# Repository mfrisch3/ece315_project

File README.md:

# starter-project

## Getting started

To make it easy for you to get started with GitLab, here's a list of recommended next steps.

Already a pro? Just edit this README.md and make it your own. Want to make it easy? [Use the template at the bottom](#editing-this-readme)!

## Add your files

- [ ] [Create](https://docs.gitlab.com/ee/user/project/repository/web_editor.html#create-a-file) or [upload](https://docs.gitlab.com/ee/user/project/repository/web_editor.html#upload-a-file) files
- [ ] [Add files using the command line](https://docs.gitlab.com/ee/gitlab-basics/add-file.html#add-a-file-using-the-command-line) or push an existing Git repository with the following command:

```
cd existing_repo
git remote add origin https://git.doit.wisc.edu/engr/ece/cmpe_courses/public/ece315/mtb/f23/starter-project.git
git branch -M main
git push -uf origin main
```

## Integrate with your tools

- [ ] [Set up project integrations](https://git.doit.wisc.edu/engr/ece/cmpe_courses/public/ece315/mtb/f23/starter-project/-/settings/integrations)

## Collaborate with your team

- [ ] [Invite team members and collaborators](https://docs.gitlab.com/ee/user/project/members/)
- [ ] [Create a new merge request](https://docs.gitlab.com/ee/user/project/merge_requests/creating_merge_requests.html)
- [ ] [Automatically close issues from merge requests](https://docs.gitlab.com/ee/user/project/issues/managing_issues.html#closing-issues-automatically)
- [ ] [Enable merge request approvals](https://docs.gitlab.com/ee/user/project/merge_requests/approvals/)
- [ ] [Set auto-merge](https://docs.gitlab.com/ee/user/project/merge_requests/merge_when_pipeline_succeeds.html)

## Test and Deploy

Use the built-in continuous integration in GitLab.

- [ ] [Get started with GitLab CI/CD](https://docs.gitlab.com/ee/ci/quick_start/index.html)
- [ ] [Analyze your code for known vulnerabilities with Static Application Security Testing(SAST)](https://docs.gitlab.com/ee/user/application_security/sast/)
- [ ] [Deploy to Kubernetes, Amazon EC2, or Amazon ECS using Auto Deploy](https://docs.gitlab.com/ee/topics/autodevops/requirements.html)
- [ ] [Use pull-based deployments for improved Kubernetes management](https://docs.gitlab.com/ee/user/clusters/agent/)
- [ ] [Set up protected environments](https://docs.gitlab.com/ee/ci/environments/protected_environments.html)

***

# Editing this README

When you're ready to make this README your own, just edit this file and use the handy template below (or feel free to structure it however you want - this is just a starting point!). Thank you to [makeareadme.com](https://www.makeareadme.com/) for this template.

## Suggestions for a good README
Every project is different, so consider which of these sections apply to yours. The sections used in the template are suggestions for most open source projects. Also keep in mind that while a README can be too long and detailed, too long is better than too short. If you think your README is too long, consider utilizing another form of documentation rather than cutting out information.

## Name
Choose a self-explaining name for your project.

## Description
Let people know what your project can do specifically. Provide context and add a link to any reference visitors might be unfamiliar with. A list of Features or a Background subsection can also be added here. If there are alternatives to your project, this is a good place to list differentiating factors.

## Badges
On some READMEs, you may see small images that convey metadata, such as whether or not all the tests are passing for the project. You can use Shields to add some to your README. Many services also have instructions for adding a badge.

## Visuals
Depending on what you are making, it can be a good idea to include screenshots or even a video (you'll frequently see GIFs rather than actual videos). Tools like ttygif can help, but check out Asciinema for a more sophisticated method.

## Installation
Within a particular ecosystem, there may be a common way of installing things, such as using Yarn, NuGet, or Homebrew. However, consider the possibility that whoever is reading your README is a novice and would like more guidance. Listing specific steps helps remove ambiguity and gets people to using your project as quickly as possible. If it only runs in a specific context like a particular programming language version or operating system or has dependencies that have to be installed manually, also add a Requirements subsection.

## Usage
Use examples liberally, and show the expected output if you can. It's helpful to have inline the smallest example of usage that you can demonstrate, while providing links to more sophisticated examples if they are too long to reasonably include in the README.

## Support
Tell people where they can go to for help. It can be any combination of an issue tracker, a chat room, an email address, etc.

## Roadmap
If you have ideas for releases in the future, it is a good idea to list them in the README.

## Contributing
State if you are open to contributions and what your requirements are for accepting them.

For people who want to make changes to your project, it's helpful to have some documentation on how to get started. Perhaps there is a script that they should run or some environment variables that they need to set. Make these steps explicit. These instructions could also be useful to your future self.

You can also document commands to lint the code or run tests. These steps help to ensure high code quality and reduce the likelihood that the changes inadvertently break something. Having instructions for running tests is especially helpful if it requires external setup, such as starting a Selenium server for testing in a browser.

## Authors and acknowledgment
Show your appreciation to those who have contributed to the project.

## License
For open source projects, say how it is licensed.

## Project status
If you have run out of energy or time for your project, put a note at the top of the README saying that development has slowed down or stopped completely. Someone may choose to fork your project or volunteer to step in as a maintainer or owner, allowing your project to keep going. You can also make an explicit request for maintainers.

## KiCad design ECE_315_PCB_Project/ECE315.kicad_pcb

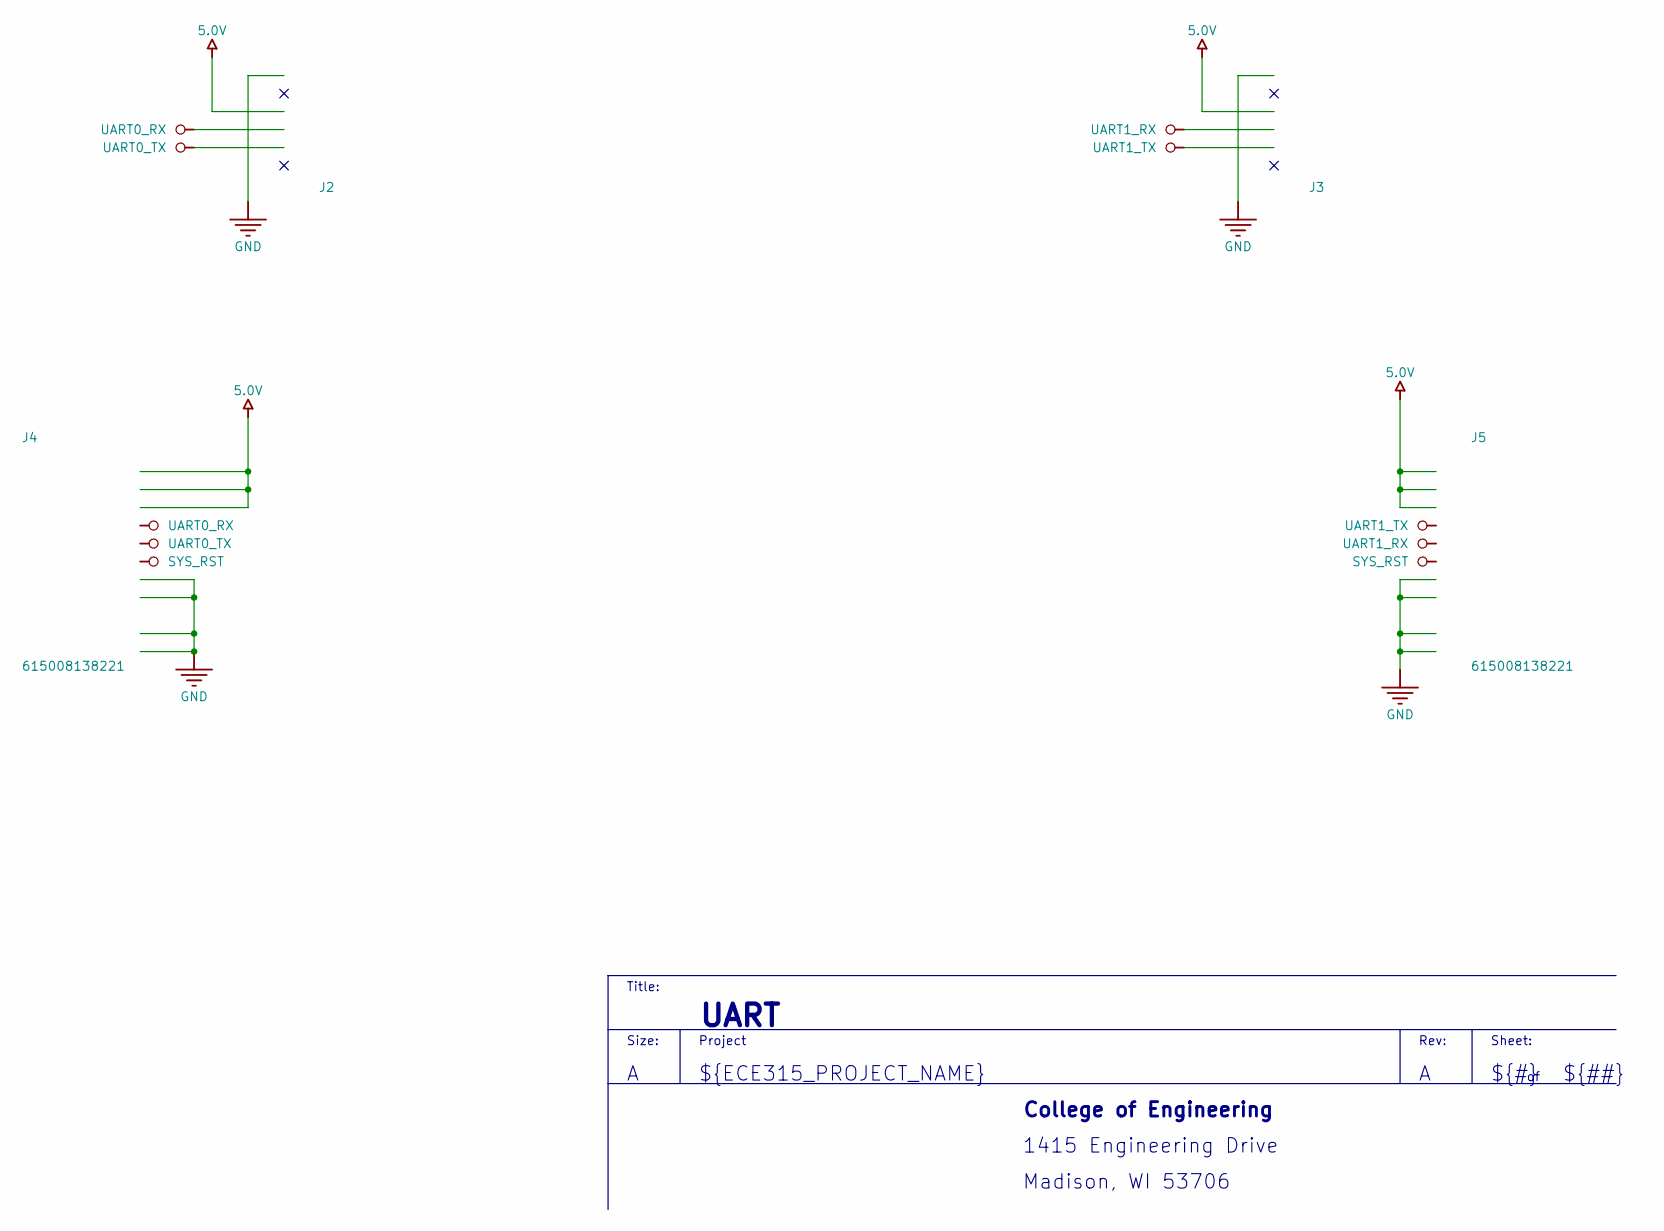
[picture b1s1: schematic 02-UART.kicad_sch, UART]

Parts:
J2, J3: HDR1X6; VOLTAGE RATING 250V; FLAMMABILITY RATING UL94 V-0; MANUFACTURER PART NUMBE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 PPPC061LGBN-RC
J4, J5: 615008138221; WITHSTANDING VOLTAGE 1000VAC; WORKING VOLTAGE 120VAC; PART NUMBER 615008138221

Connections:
5.0V: J2.3, J3.3, J4.1, J4.2, J4.3, J5.1, J5.2, J5.3; also elsewhere on the board
GND: J2.1, J3.1, J4.7, J4.8, J4.S1, J4.S2, J5.7, J5.8, J5.S1, J5.S2; also elsewhere on the board
SYS_RST: J4.6, J5.6; also elsewhere on the board
UART0_RX: J2.4, J4.4; also elsewhere on the board
UART0_TX: J2.5, J4.5; also elsewhere on the board
UART1_RX: J3.4, J5.5; also elsewhere on the board
UART1_TX: J3.5, J5.4; also elsewhere on the board

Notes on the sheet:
Rev:
Sheet:
${REVISION}
Size:
${TITLE}
${#}
Project
College of Engineering
Title:
${ECE315_PROJECT_NAME}
1415 Engineering Drive
Madison, WI 53706
${##}

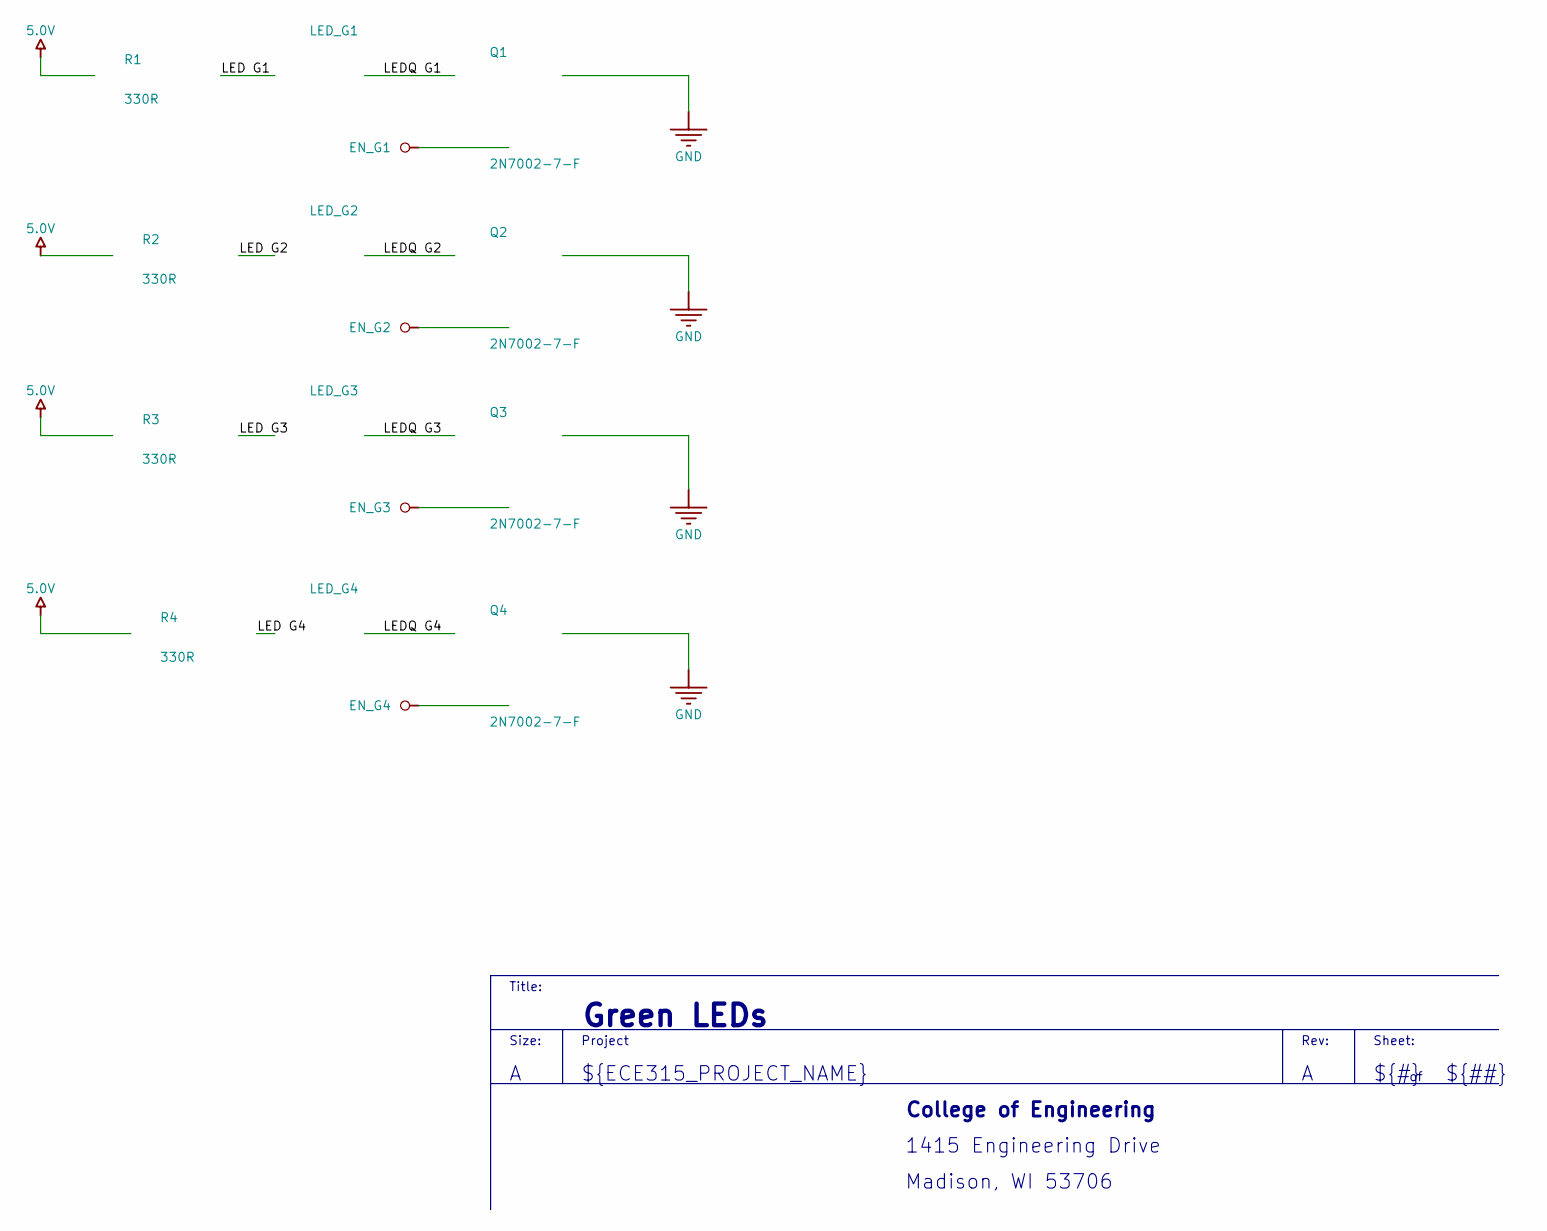
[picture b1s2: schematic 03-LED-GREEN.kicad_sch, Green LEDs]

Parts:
LED_G1, LED_G2, LED_G3, LED_G4: 150120GS75000; WL-SMCW_1206_150120xx75000; REVERSE VOLTAGE 5V; FORWARD VOLTAGE 3.2V; MANUFACTURER PART NUMBER 150120GS75000
Q1, Q2, Q3, Q4: 2N7002-7-F; FP-SOT23-MFG; CURRENT RATING 115mA; VOLTAGE RATING (DC) 60V
R1, R2, R3, R4: 330R; FP-CRCW1206-e3-IPC_A; VOLTAGE RATING 200V; VOLTAGE RATING (DC) 200V

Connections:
5.0V: R1.1, R2.1, R3.1, R4.1; also elsewhere on the board
EN_G1: Q1.1 (G); also elsewhere on the board
EN_G2: Q2.1 (G); also elsewhere on the board
EN_G3: Q3.1 (G); also elsewhere on the board
EN_G4: Q4.1 (G); also elsewhere on the board
GND: Q1.2 (S), Q2.2 (S), Q3.2 (S), Q4.2 (S); also elsewhere on the board
LED G1: LED_G1.2 (A), R1.2
LED G2: LED_G2.2 (A), R2.2
LED G3: LED_G3.2 (A), R3.2
LED G4: LED_G4.2 (A), R4.2
LEDQ G1: LED_G1.1 (K), Q1.3 (D)
LEDQ G2: LED_G2.1 (K), Q2.3 (D)
LEDQ G3: LED_G3.1 (K), Q3.3 (D)
LEDQ G4: LED_G4.1 (K), Q4.3 (D)

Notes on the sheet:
${ECE315_PROJECT_NAME}
College of Engineering
${TITLE}
Size:
${##}
${#}
Rev:
1415 Engineering Drive
Madison, WI 53706
Sheet:
${REVISION}
Title:
Project

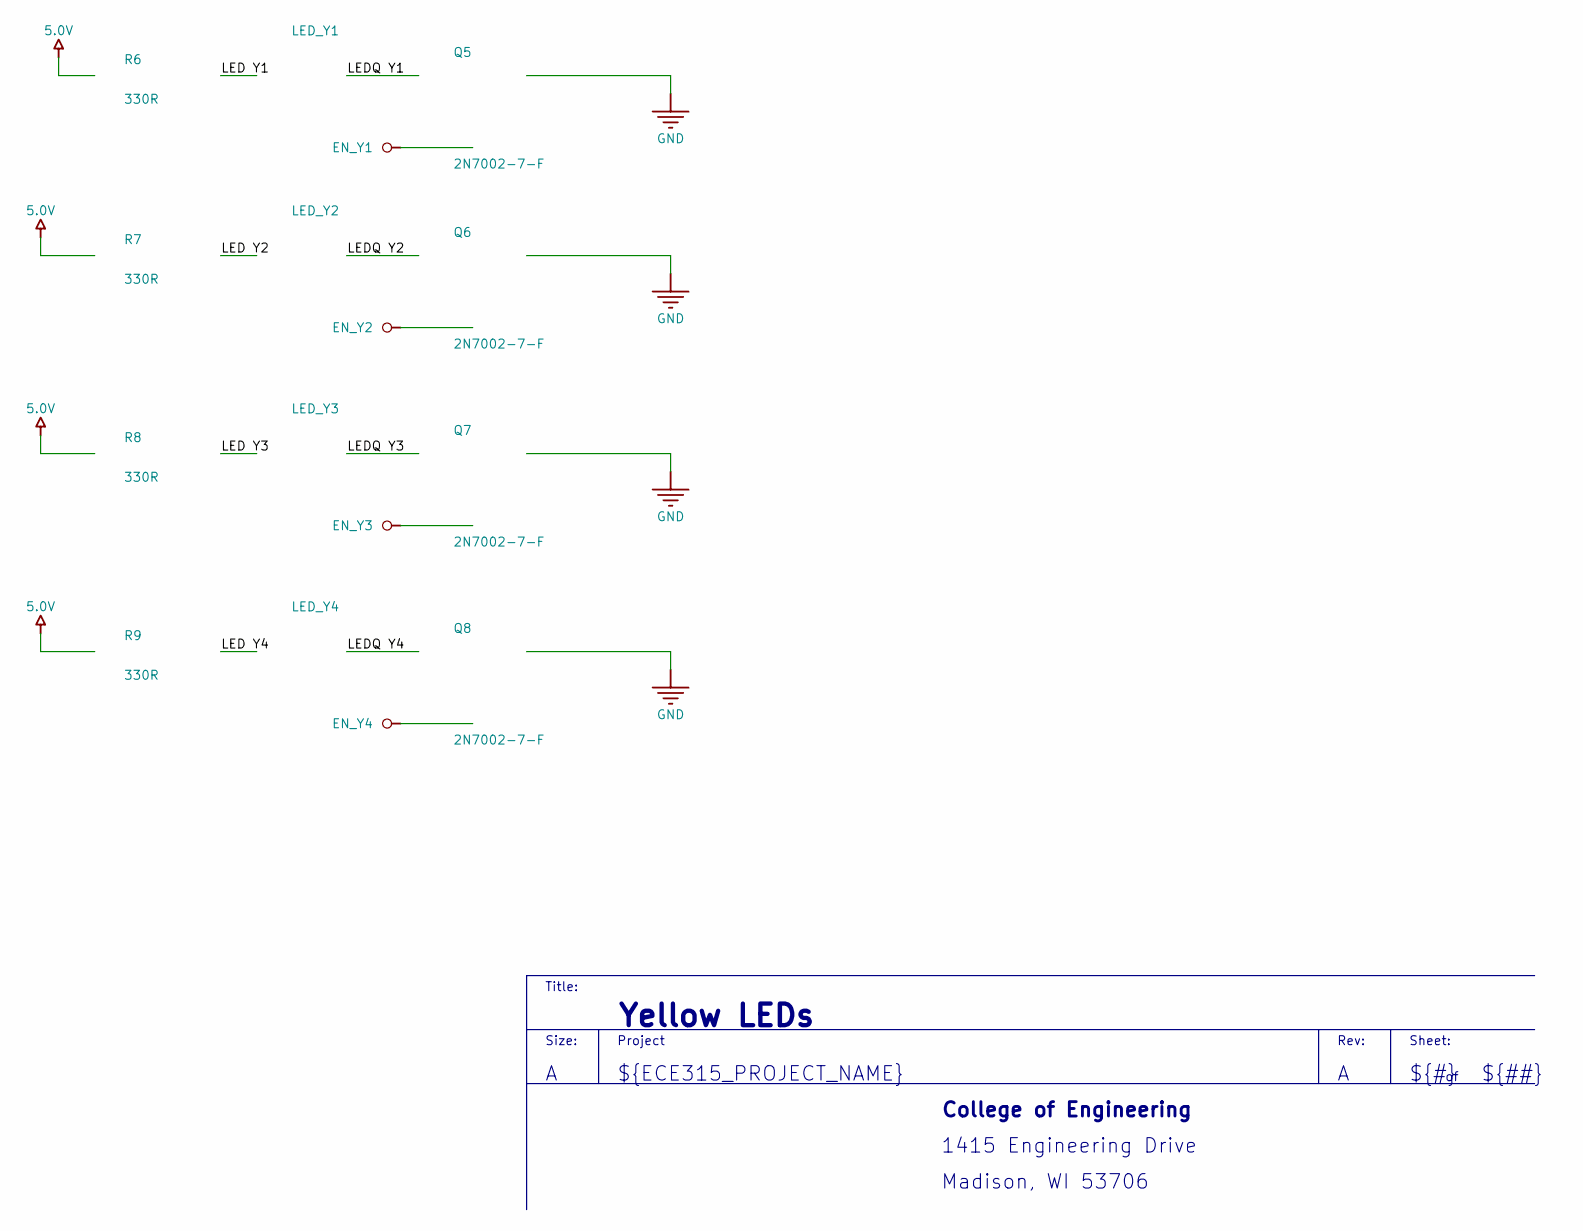
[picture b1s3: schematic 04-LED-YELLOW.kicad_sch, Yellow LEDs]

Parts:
LED_Y1, LED_Y2, LED_Y3, LED_Y4: SML-LX1206YC-TR; LUMX-SML-LX1206YC-TR_V; MILLICANDELA RATING 6mcd; VOLTAGE - FORWARD (VF) 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 2.1V; MANUFACTURER PART NUMBE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 SML-LX1206YC-TR
Q5, Q6, Q7, Q8: 2N7002-7-F; FP-SOT23-MFG; CURRENT RATING 115mA; VOLTAGE RATING (DC) 60V
R6, R7, R8, R9: 330R; FP-CRCW1206-e3-IPC_A; VOLTAGE RATING 200V; VOLTAGE RATING (DC) 200V

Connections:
5.0V: R6.1, R7.1, R8.1, R9.1; also elsewhere on the board
EN_Y1: Q5.1 (G); also elsewhere on the board
EN_Y2: Q6.1 (G); also elsewhere on the board
EN_Y3: Q7.1 (G); also elsewhere on the board
EN_Y4: Q8.1 (G); also elsewhere on the board
GND: Q5.2 (S), Q6.2 (S), Q7.2 (S), Q8.2 (S); also elsewhere on the board
LED Y1: LED_Y1.1 (A), R6.2
LED Y2: LED_Y2.1 (A), R7.2
LED Y3: LED_Y3.1 (A), R8.2
LED Y4: LED_Y4.1 (A), R9.2
LEDQ Y1: LED_Y1.2 (K), Q5.3 (D)
LEDQ Y2: LED_Y2.2 (K), Q6.3 (D)
LEDQ Y3: LED_Y3.2 (K), Q7.3 (D)
LEDQ Y4: LED_Y4.2 (K), Q8.3 (D)

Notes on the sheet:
Title:
Madison, WI 53706
Sheet:
${TITLE}
Size:
College of Engineering
Project
${ECE315_PROJECT_NAME}
1415 Engineering Drive
${#}
${##}
Rev:
${REVISION}

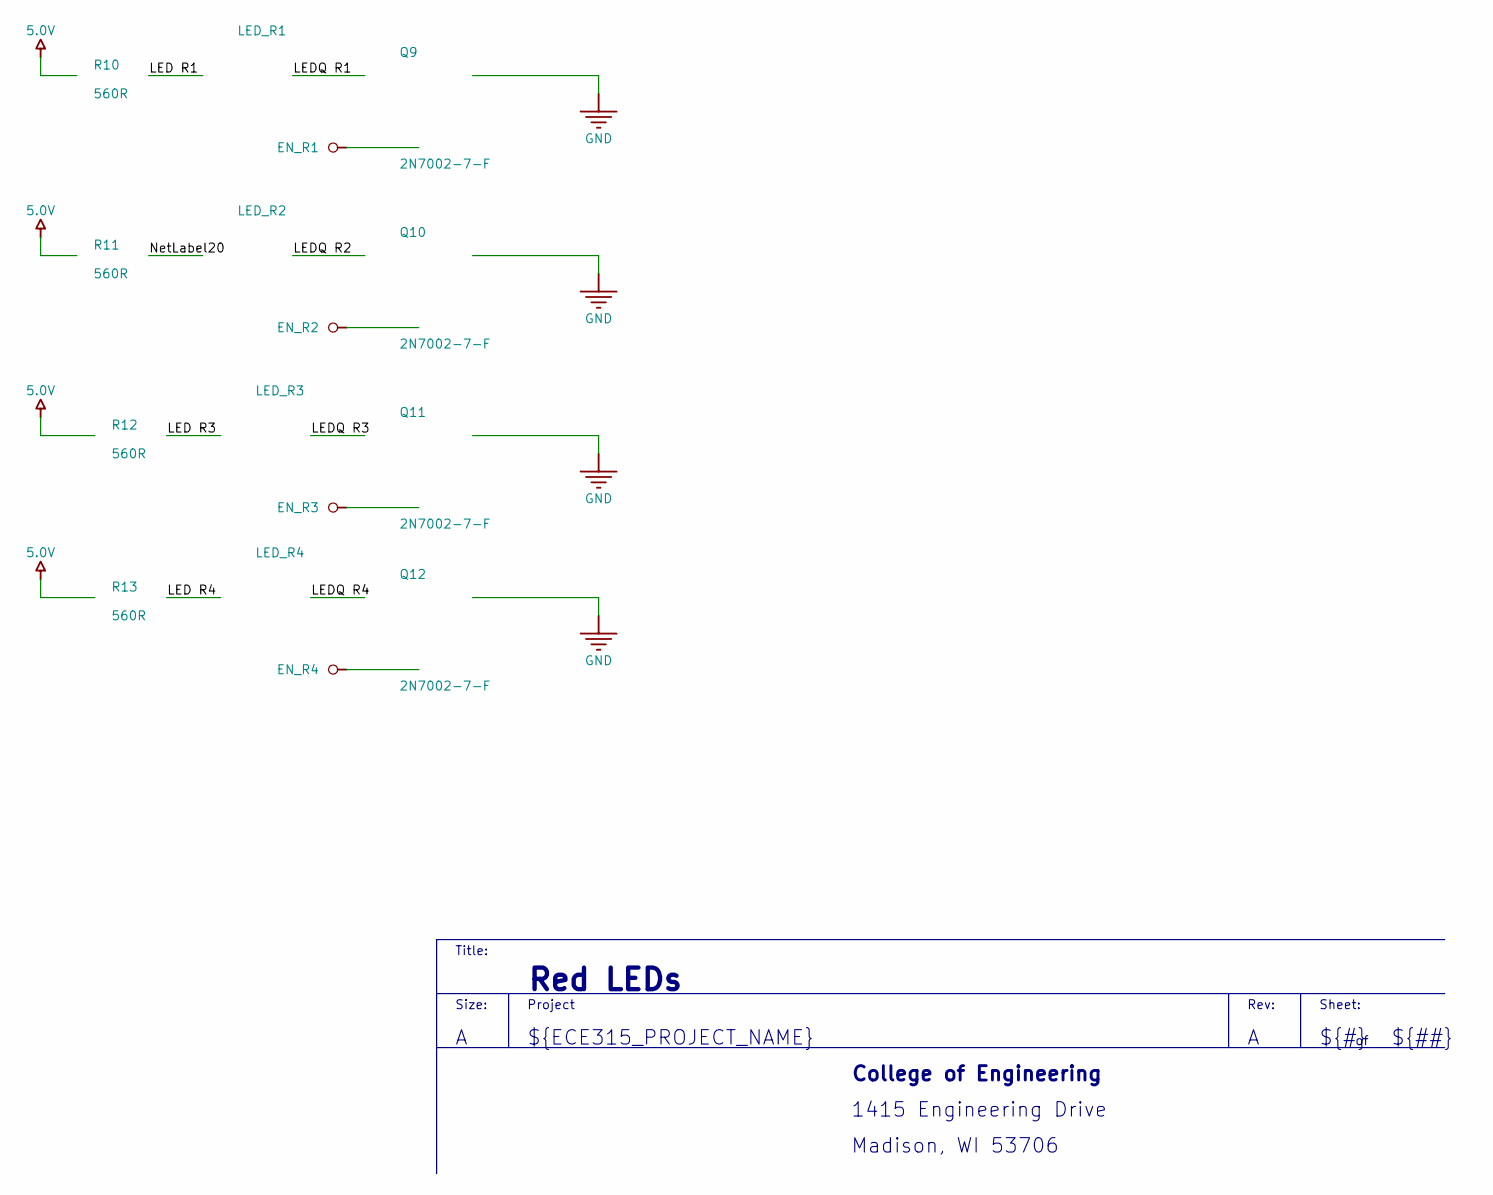
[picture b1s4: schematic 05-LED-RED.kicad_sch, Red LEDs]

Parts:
LED_R1, LED_R2, LED_R3, LED_R4: SML-LX1206IC-TR; LUMX-SML-LX1206IC_V; REVERSE VOLTAGE 5(Min)V; FORWARD VOLTAGE 2.6V; PART NO SML-LX1206IC-TR
Q9, Q10, Q11, Q12: 2N7002-7-F; FP-SOT23-MFG; CURRENT RATING 115mA; VOLTAGE RATING (DC) 60V
R10, R11, R12, R13: 560R; RESC3216X70X50LL05T20; PART NUMBER ERJ8ENF5600V

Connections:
5.0V: R10.1, R11.1, R12.1, R13.1; also elsewhere on the board
EN_R1: Q9.1 (G); also elsewhere on the board
EN_R2: Q10.1 (G); also elsewhere on the board
EN_R3: Q11.1 (G); also elsewhere on the board
EN_R4: Q12.1 (G); also elsewhere on the board
GND: Q9.2 (S), Q10.2 (S), Q11.2 (S), Q12.2 (S); also elsewhere on the board
LED R1: LED_R1.1 (A), R10.2
LED R3: LED_R3.1 (A), R12.2
LED R4: LED_R4.1 (A), R13.2
LEDQ R1: LED_R1.2 (K), Q9.3 (D)
LEDQ R2: LED_R2.2 (K), Q10.3 (D)
LEDQ R3: LED_R3.2 (K), Q11.3 (D)
LEDQ R4: LED_R4.2 (K), Q12.3 (D)
NetLabel20: LED_R2.1 (A), R11.2

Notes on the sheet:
${##}
Rev:
${TITLE}
${ECE315_PROJECT_NAME}
Title:
${REVISION}
${#}
College of Engineering
Project
Madison, WI 53706
Sheet:
1415 Engineering Drive
Size:

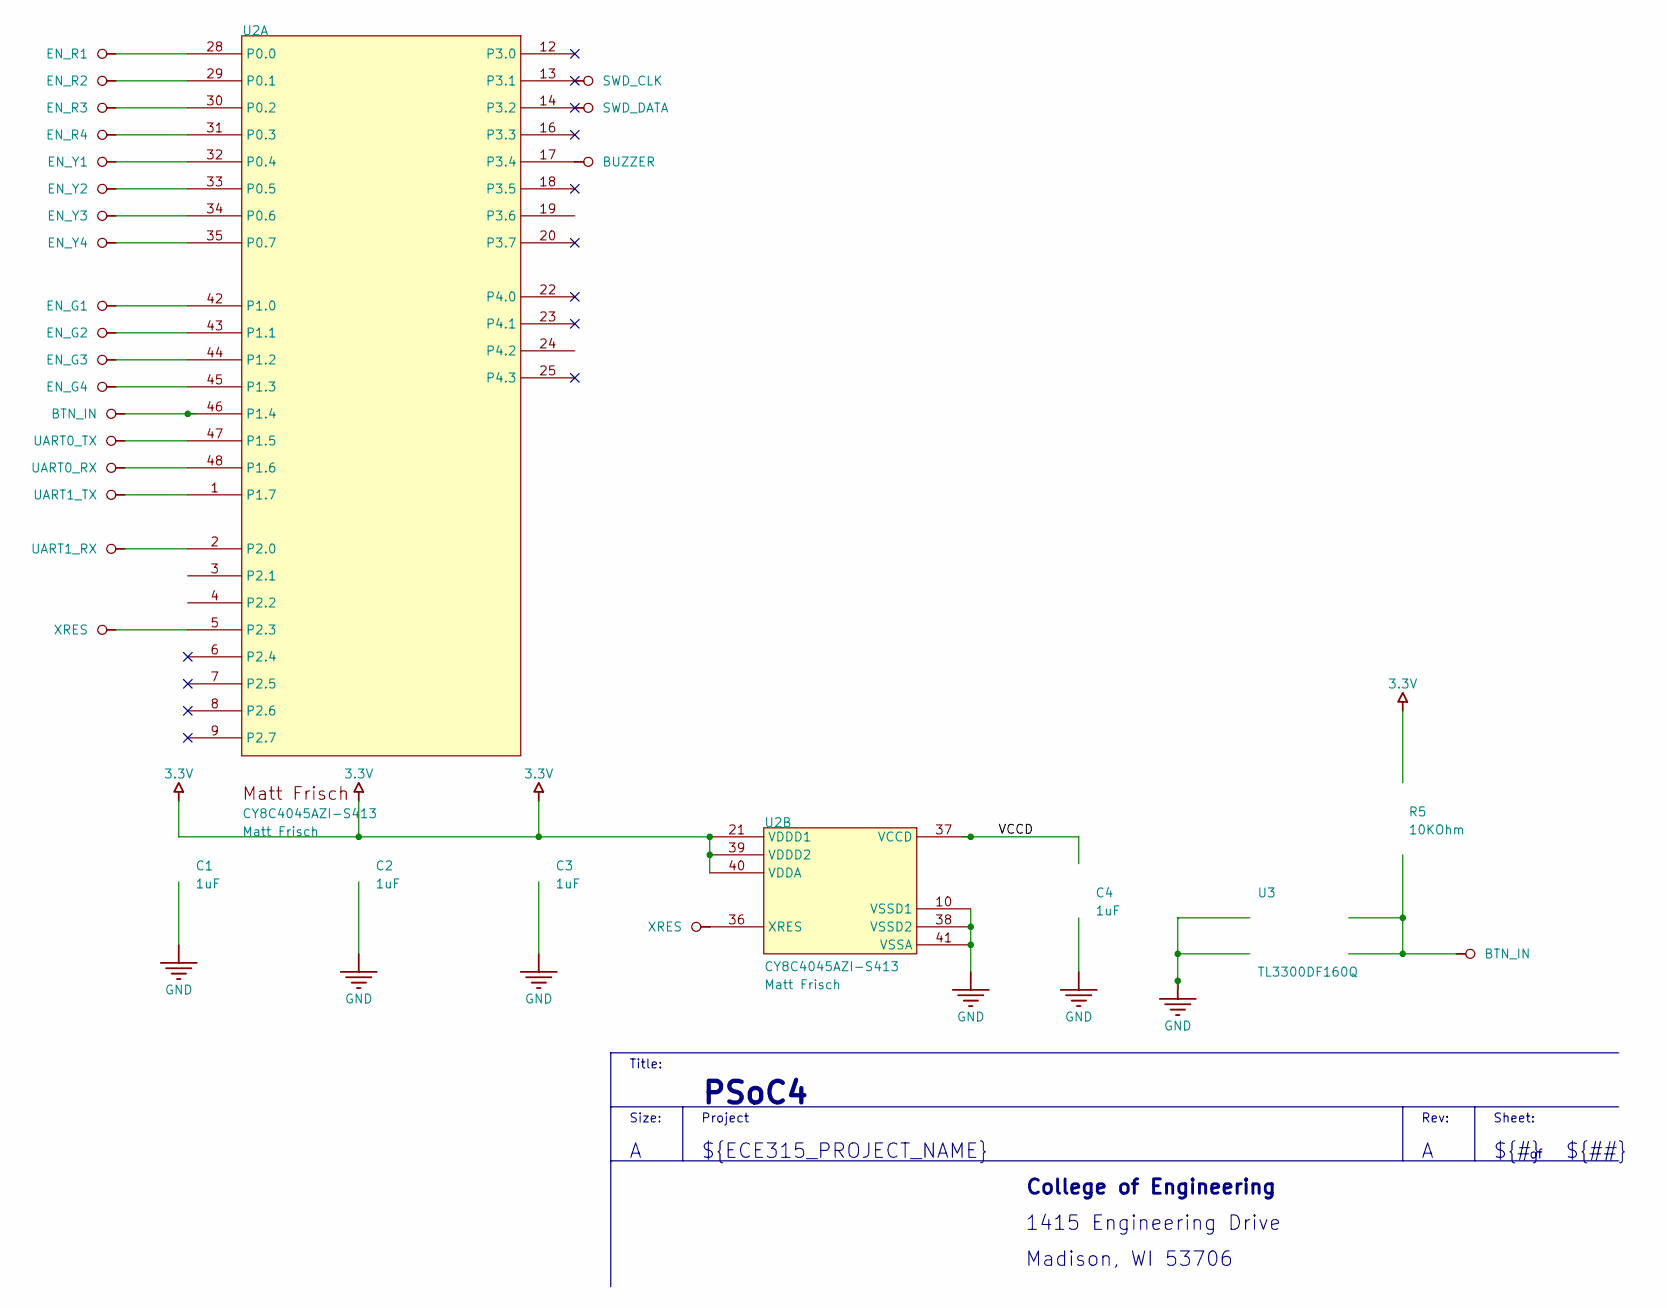
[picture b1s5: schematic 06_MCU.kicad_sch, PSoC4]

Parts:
C1, C2, C3, C4: 1uF; CAPC3216X180X50ML20T25; VOLTAGE RATING DC 25V; TOLERANCE 10%
R5: 10KOhm; RESC3116X65X40ML10T20; TOLERANCE 1%; VOLTAGE RATING 200V
U2: CY8C4045AZI-S413; TQFP48_7X7; MANUFACTURER PART NUMBE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 CY8C4045AZI-S413
U3: TL3300DF160Q; CONTACT RATING @ VOLTAGE 0.05A @ 12VDC; CURRENT RATING 50mA; MANUFACTURER PART NUMBER TL3300DF160Q

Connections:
3.3V: C1.2, C2.2, C3.2, R5.1, U2.21 (VDDD1), U2.39 (VDDD2), U2.40 (VDDA); also elsewhere on the board
BTN_IN: R5.2, U2.46 (P1.4), U3.3, U3.4 (VCCIO)
BUZZER: U2.17 (P3.4); also elsewhere on the board
EN_G1: U2.42 (P1.0); also elsewhere on the board
EN_G2: U2.43 (P1.1); also elsewhere on the board
EN_G3: U2.44 (P1.2); also elsewhere on the board
EN_G4: U2.45 (P1.3); also elsewhere on the board
EN_R1: U2.28 (P0.0); also elsewhere on the board
EN_R2: U2.29 (P0.1); also elsewhere on the board
EN_R3: U2.30 (P0.2); also elsewhere on the board
EN_R4: U2.31 (P0.3); also elsewhere on the board
EN_Y1: U2.32 (P0.4); also elsewhere on the board
EN_Y2: U2.33 (P0.5); also elsewhere on the board
EN_Y3: U2.34 (P0.6); also elsewhere on the board
EN_Y4: U2.35 (P0.7); also elsewhere on the board
GND: C1.1, C2.1, C3.1, C4.1, U2.10 (VSSD1), U2.38 (VSSD2), U2.41 (VSSA), U3.1, U3.2; also elsewhere on the board
SWD_CLK: U2.3 (P2.1); also elsewhere on the board
SWD_DATA: U2.4 (P2.2); also elsewhere on the board
UART0_RX: U2.48 (P1.6); also elsewhere on the board
UART0_TX: U2.47 (P1.5); also elsewhere on the board
UART1_RX: U2.2 (P2.0); also elsewhere on the board
UART1_TX: U2.1 (P1.7); also elsewhere on the board
VCCD: C4.2, U2.37 (VCCD)
XRES: U2.5 (P2.3), U2.36 (XRES); also elsewhere on the board

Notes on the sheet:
${TITLE}
Madison, WI 53706
${##}
Project
1415 Engineering Drive
Sheet:
${ECE315_PROJECT_NAME}
Size:
College of Engineering
Title:
Rev:
${REVISION}
${#}

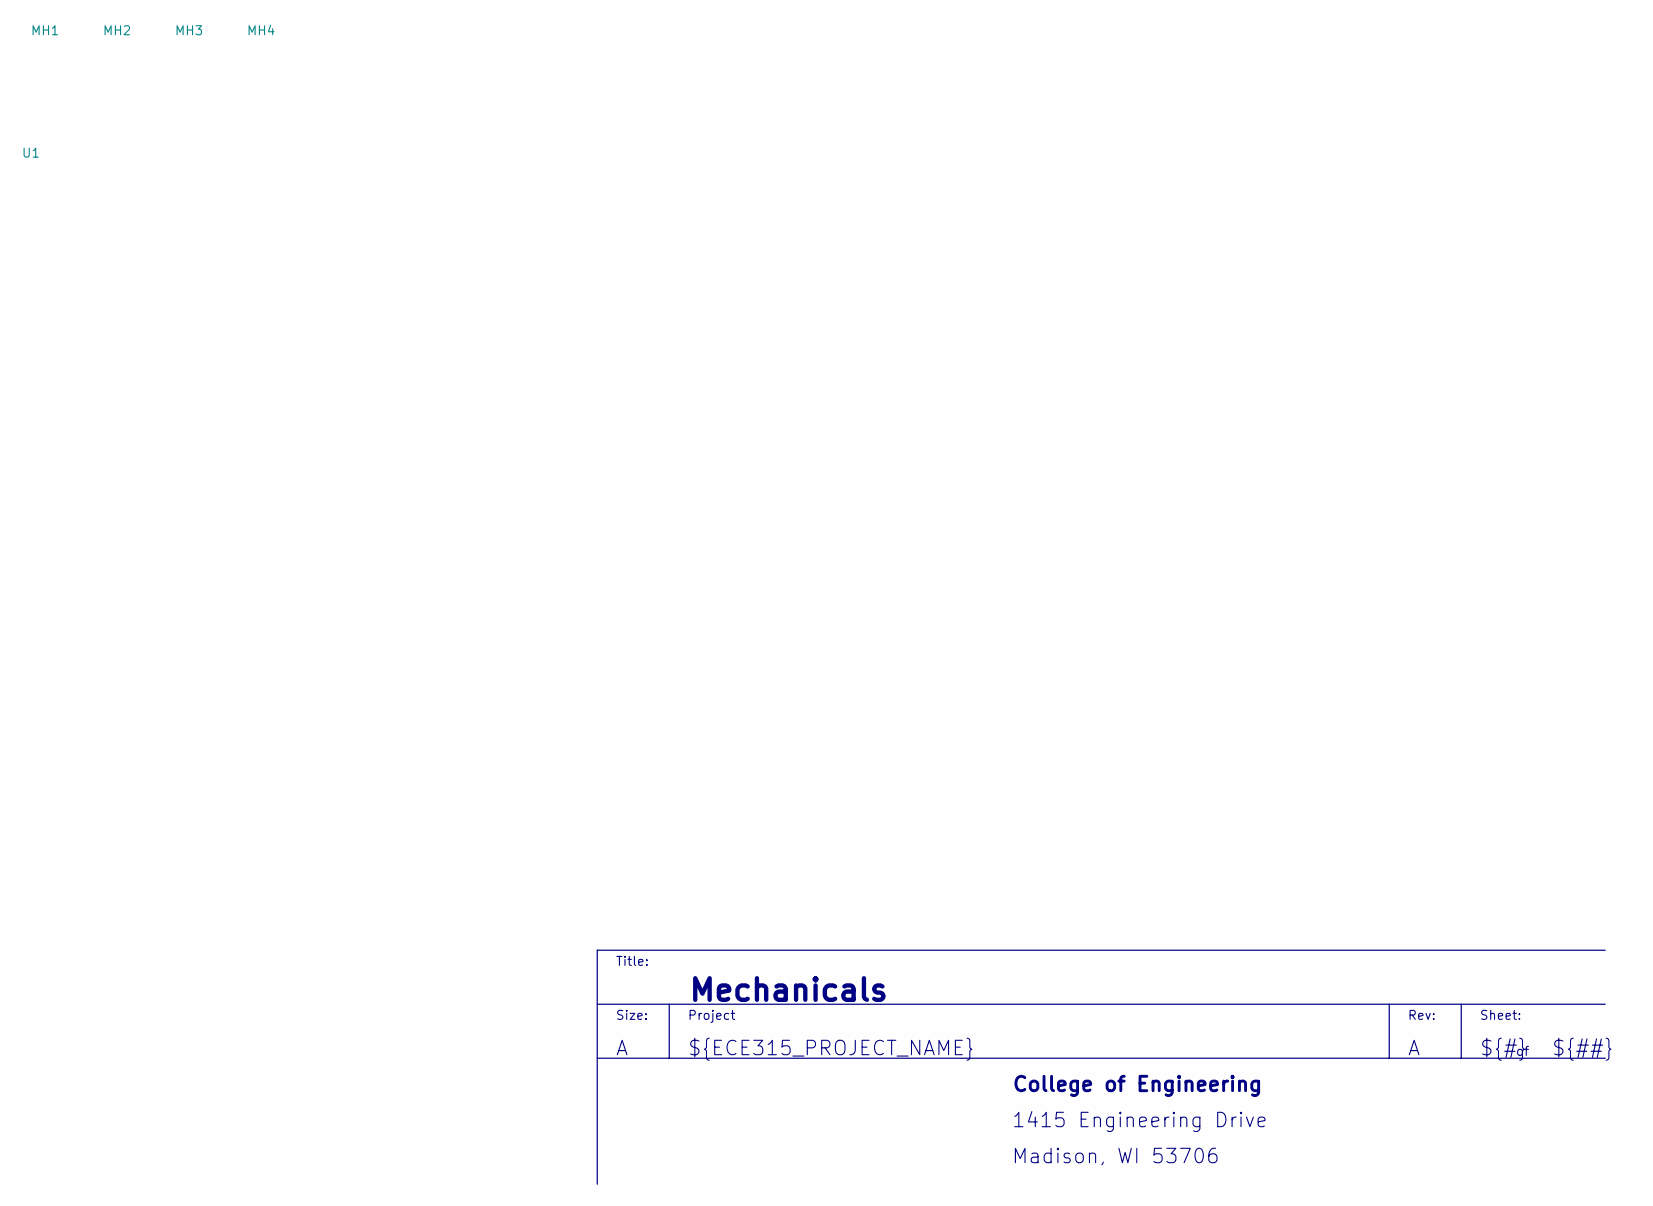
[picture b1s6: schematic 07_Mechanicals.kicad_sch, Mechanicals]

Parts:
MH1, MH2, MH3, MH4: MHOLE_2_55MM; MANUFACTURER PART NUMBER UW MTHOLE
U1: Bucky; WalkingBucky; MANUFACTURER PART NUMBER UW Bucky

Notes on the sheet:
${REVISION}
Rev:
Project
${TITLE}
${#}
College of Engineering
Title:
1415 Engineering Drive
${ECE315_PROJECT_NAME}
Sheet:
Madison, WI 53706
Size:
${##}

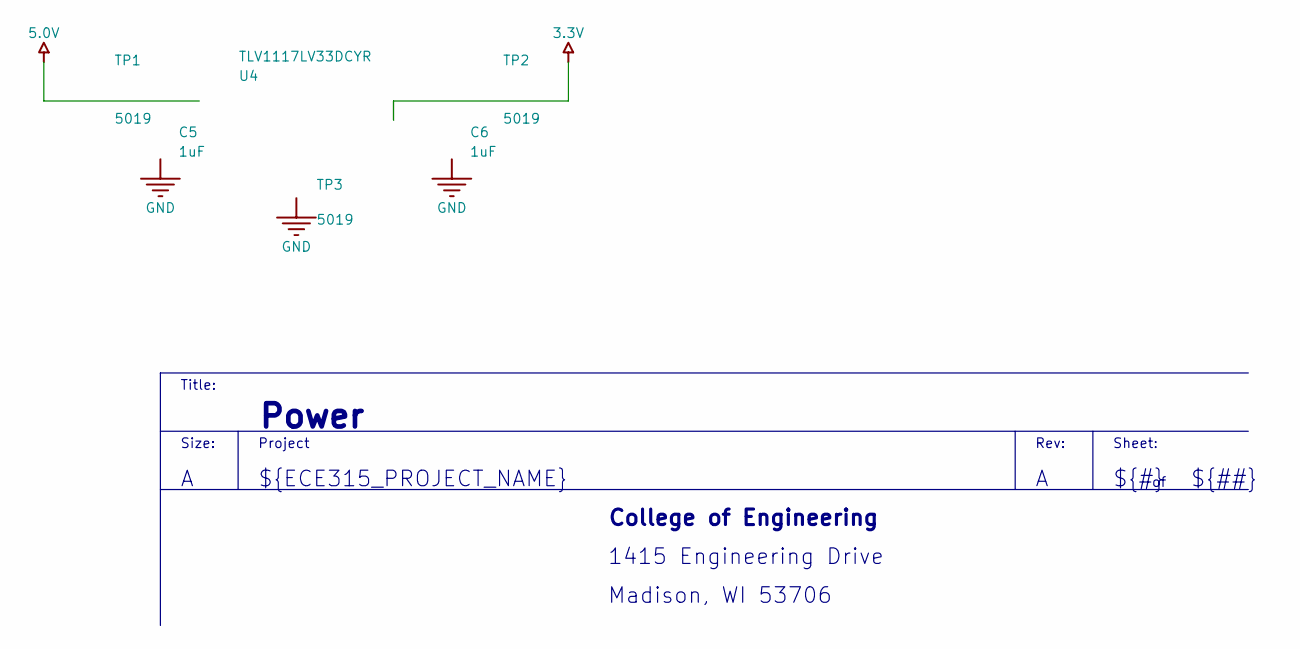
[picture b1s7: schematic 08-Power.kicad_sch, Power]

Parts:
C5, C6: 1uF; CAPC3216X180X50ML20T25; VOLTAGE RATING DC 25V; TOLERANCE 10%
TP1, TP2, TP3: 5019; KSTN-5019_V
U4: TLV1117LV33DCYR; DCY0004A_N; PARTNUMBER TLV1117LV33DCYR

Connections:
3.3V: C6.2, TP2.1, U4.2 (OUT), U4.4 (OUT); also elsewhere on the board
5.0V: C5.2, TP1.1, U4.3 (IN); also elsewhere on the board
GND: C5.1, C6.1, TP3.1, U4.1 (GND); also elsewhere on the board

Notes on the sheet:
Title:
${ECE315_PROJECT_NAME}
${REVISION}
${#}
Rev:
Sheet:
${##}
${TITLE}
College of Engineering
Size:
Madison, WI 53706
Project
1415 Engineering Drive

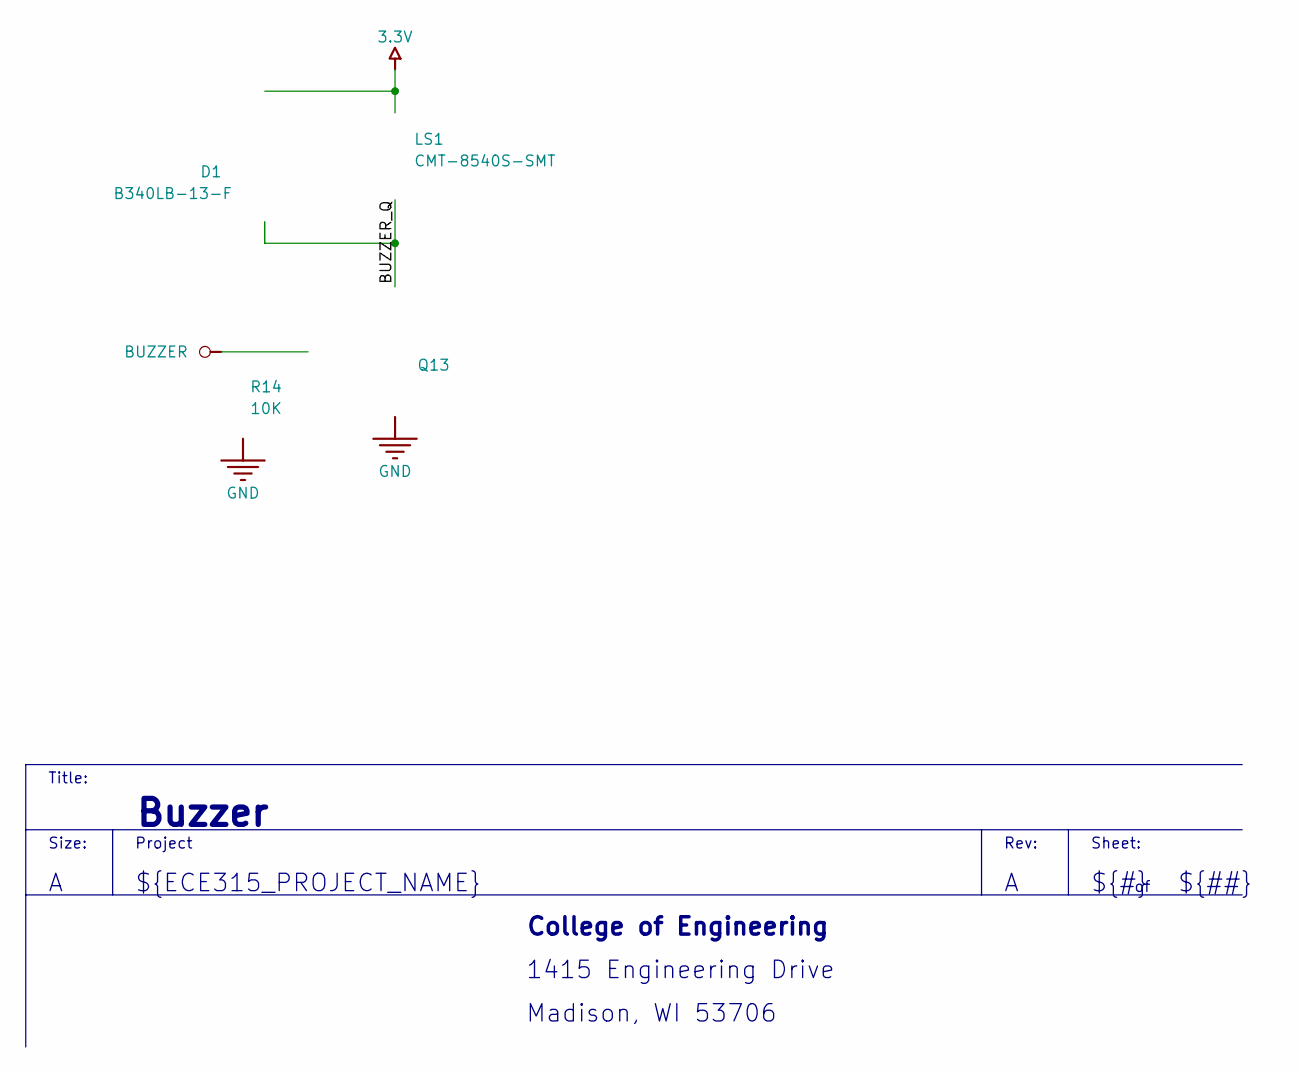
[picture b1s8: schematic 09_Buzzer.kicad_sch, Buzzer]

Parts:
D1: B340LB-13-F; FP-SMB-MFG; REVERSE VOLTAGE 40V; FORWARD VOLTAGE 450mV; MANUFACTURER PART NUMBER B340LB-13-F; DIGIKEY DESCRIPTION DIODE SCHOTTKY 40V 3A SMB
LS1: CMT-8540S-SMT; CUI_CMT-8540S-SMT; VOLTAGE RATING 5V; MANUFACTURER PART NUMBE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 CMT-8540S-SMT-TR
Q13: 2N7002-7-F; FP-SOT23-MFG; CURRENT RATING 115mA; VOLTAGE RATING (DC) 60V; MANUFACTURER PART NUMBE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 2N7002-7-F
R14: RC1206FR-0710KL; RESC3116X65X40ML10T20; TOLERANCE 1%; VOLTAGE RATING 200V; MANUFACTURER PART NUMBER RC1206FR-0710KL

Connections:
3.3V: D1.1 (C), LS1.P; also elsewhere on the board
BUZZER: Q13.1 (G), R14.2; also elsewhere on the board
BUZZER_Q: D1.2 (A), LS1.N, Q13.3 (D)
GND: Q13.2 (S), R14.1; also elsewhere on the board

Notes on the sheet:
${REVISION}
${TITLE}
Size:
Sheet:
Title:
${##}
Rev:
College of Engineering
${#}
1415 Engineering Drive
Madison, WI 53706
Project
${ECE315_PROJECT_NAME}

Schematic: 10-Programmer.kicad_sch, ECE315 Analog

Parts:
J1: 10129380-905002BLF; AMPHENOL_10129380-905002BLF; MANUFACTURER PART NUMBE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 10129380-905002BLF
R15, R16: RC1206FR-0710KL; RESC3116X65X40ML10T20; TOLERANCE 1%; VOLTAGE RATING 200V; MANUFACTURER PART NUMBER RC1206FR-0710KL
SW1: B3U-1000P; FP-B3U-1000P-MFG; MAX VOLTAGE RATING (DC) 12V; CURRENT RATING 50mA; MANUFACTURER PART NUMBER B3U-1000P
U5: SN74AHC1G08DBVR; FP-DBV0005A-MFG; MANUFACTURER PART NUMBER SN74AHC1G08DBVR; DIGIKEY DESCRIPTION IC GATE AND 1CH 2-INP SOT23-5

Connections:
3.3V: J1.5, R15.2, R16.2, U5.5 (VCC); also elsewhere on the board
GND: J1.4, SW1.1, U5.3 (GND); also elsewhere on the board
MCU_RST: J1.3, R16.1, SW1.2, U5.2 (B)
SWD_CLK: J1.2; also elsewhere on the board
SWD_DATA: J1.1; also elsewhere on the board
SYS_RST: R15.1, U5.1 (A); also elsewhere on the board
XRES: U5.4 (Y); also elsewhere on the board

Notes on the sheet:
Madison, WI 53706
Project
${##}
${#}
1415 Engineering Drive
Title:
Rev:
${ECE315_PROJECT_NAME}
Size:
College of Engineering
${TITLE}
${REVISION}
Sheet:
5 Pin MiniProg4 Header
Push button reset for MCU
